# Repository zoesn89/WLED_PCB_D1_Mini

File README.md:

# WLED PCB for D1 Mini
A PCB for WLED with WeMos D1 Mini and SN74AHCT125N level shifter.

Recommended software: [WLED](https://github.com/Aircoookie/WLED)

## Preview

## Components

- C1: Capacitor Radial 1000μF
- U1: WeMos D1 Mini
- U2: level shifter SN74AHCT125N
- R1: Resistor 330Ω

## GPIO

- GPIO3 = CLK line of addressable strip
- GPIO4 = Data line of addressable strip

## Gerber Files
[Gerber-Files](https://github.com/zoesn89/WLED_PCB_D1_Mini/releases)

## Enclosure STL-Files
[STL-Files](https://github.com/zoesn89/WLED_PCB_D1_Mini/tree/main/Enclosure)

## License

The MIT License (MIT)

Copyright (c) 2021 Felix Zösch

Permission is hereby granted, free of charge, to any person obtaining a copy
of this software and associated documentation files (the "Software"), to deal
in the Software without restriction, including without limitation the rights
to use, copy, modify, merge, publish, distribute, sublicense, and/or sell
copies of the Software, and to permit persons to whom the Software is
furnished to do so, subject to the following conditions:

The above copyright notice and this permission notice shall be included in
all copies or substantial portions of the Software.

THE SOFTWARE IS PROVIDED "AS IS", WITHOUT WARRANTY OF ANY KIND, EXPRESS OR
IMPLIED, INCLUDING BUT NOT LIMITED TO THE WARRANTIES OF MERCHANTABILITY,
FITNESS FOR A PARTICULAR PURPOSE AND NONINFRINGEMENT. IN NO EVENT SHALL THE
AUTHORS OR COPYRIGHT HOLDERS BE LIABLE FOR ANY CLAIM, DAMAGES OR OTHER
LIABILITY, WHETHER IN AN ACTION OF CONTRACT, TORT OR OTHERWISE, ARISING FROM,
OUT OF OR IN CONNECTION WITH THE SOFTWARE OR THE USE OR OTHER DEALINGS IN
THE SOFTWARE.

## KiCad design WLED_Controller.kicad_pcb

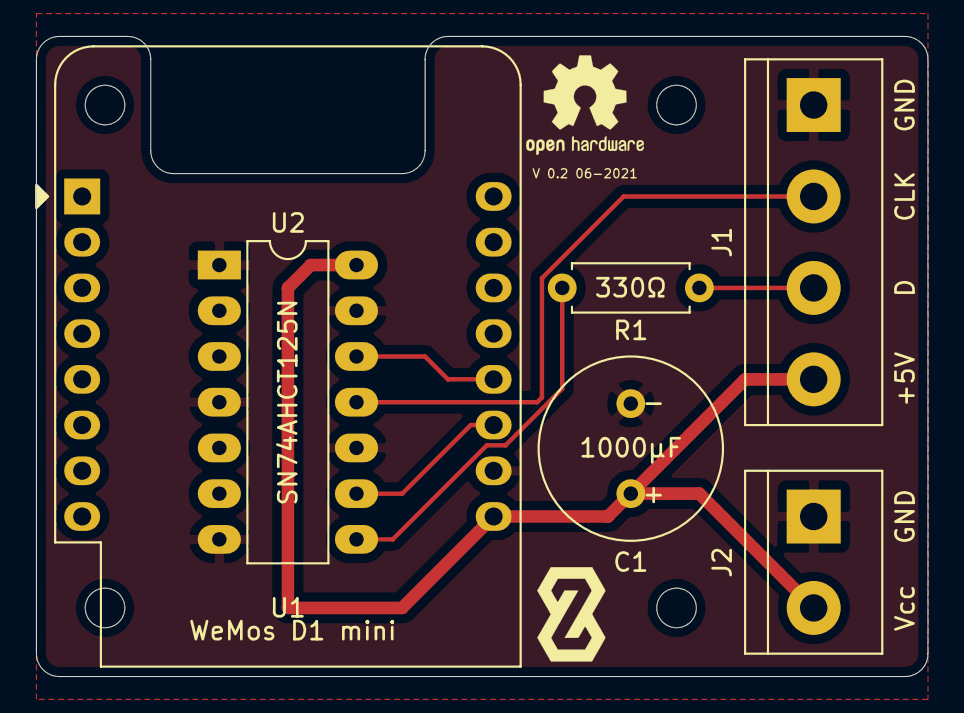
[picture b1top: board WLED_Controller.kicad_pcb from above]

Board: 2 copper layers, 49.5 x 35.6 mm, 6 parts (0 on the bottom side), 7 nets.

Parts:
C1: 1000µF; C_Radial_D10.0mm_H20.0mm_P5.00mm
J1: Screw_Terminal_01x04; TerminalBlock_bornier-4_P5.08mm
J2: Screw_Terminal_01x02; TerminalBlock_bornier-2_P5.08mm
R1: 330Ω; R_Axial_DIN0207_L6.3mm_D2.5mm_P7.62mm_Horizontal
U1: WeMos D1 mini; WEMOS_D1_mini_light
U2: SN74AHCT125N; DIP-14_W7.62mm_LongPads

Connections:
+5V: C1.1, J1.4, J2.2, U1.9, U2.14
GND: C1.2, J1.1, J2.1, U1.10, U2.1, U2.4, U2.7, U2.10, U2.13
unnamed: J1.2, U2.11
unnamed: J1.3, R1.1
unnamed: R1.2, U2.8
unnamed: U1.11, U2.9
unnamed: U1.12, U2.12

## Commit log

2021-06-15 v0.2
2021-06-15 update files
2021-06-15 Create LICENSE
2021-08-02 added enclosure files
2021-09-02 Added WLED-Controller Schematic
2021-09-02 deleted cache files
